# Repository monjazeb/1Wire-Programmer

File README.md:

# UNDER CONSTRUCTION
this project is not finished yet.

## Todo
- [x] GUI and Serial connection
- [ ] 1wire
    - [x] read
    - [ ] write
        - [x] change pcb to apply 12v to wire pin for write
        - [ ] edit firmware to write on chip
- [ ] EEPROM
    - [ ] read operation
        - [ ] it is erratic, why?
    - [ ] write operation
- [ ] Complete Readme.md file for help
- [ ] Create Installation package
- [ ] :tada:

## 2 in 1 Programmer1
> This project is actually a combination of 2 projects. I needed a _1Wire programmer_ and also an _EEPROM parallel programmer_. Since I had to use an _Arduino Mega_ board, I had plenty of space and `GPIO` to integrate both in one place :wink:.

You can contact me at [github](https://github.com/monjazeb) or by this [email](mailto:armonj@gmail.com).

***Thanks.***

## 1Wire Programmer
1Wire EEPROM programmer using Arduino. 

## EEPROM Progarmmer
I used [mint64](https://mint64.home.blog/2018/07/29/parallel-nor-flash-eeprom-programmer-using-an-arduino-part-1-the-sst39sf040-and-planning/)'s project as base and added essencial functionalities I needed.

## GUI

## Board

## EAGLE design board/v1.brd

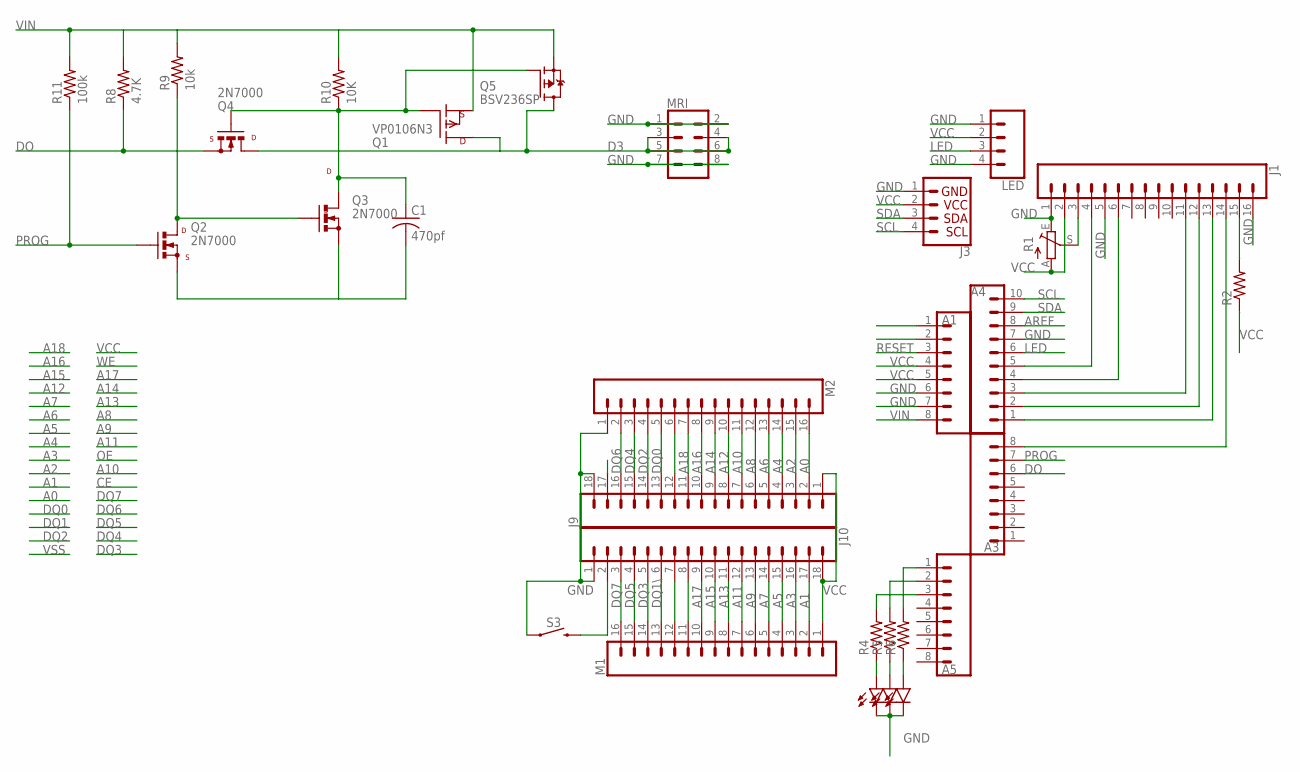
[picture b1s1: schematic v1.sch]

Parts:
A1, A3, A5: CONN_08FEMALE_LOCK; 1X08_FEMALE_LOCK
A4: CONN_10LOCK; 1X10_LOCK
C1: 470pf; C025-025X050
D1, D2, D3: LED3MM; LED_3MM
J1: CONN_16LOCK; 1X16_LOCK
J3: I2C_STANDARD; 1X04
J9, J10: CONN_18SILK; 1X18
LED: CONN_04LOCK; 1X04_LOCK
M1, M2: CONN_16MACHIINE-PIN_LOCK; 1X16_MACHINE-PIN-HEADER_LOCK.004
MRI: CONN_04X2; 2X4
Q1: VP0106N3; TO92-
Q2, Q3, Q4: 2N7000; TO92-LINE
Q5: BSV236SP; SOT363_INFINEON
R1: TRIM_EU-B64Y; B64Y
R2, R4, R5, R6: R-US_0309/10; 0309/10
R8: 4.7K; 0207/2V
R9: 10k; 0309/10
R10: 10K; 0207/2V
R11: 100k; 0309/10
S3: MOMENTARY-SWITCH-SPST-PTH-6.0MM; TACTILE_SWITCH_PTH_6.0MM

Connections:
A0: J9.2, M2.16
A1: J10.17, M1.2
A2: J9.3, M2.15
A3: J10.16, M1.3
A4: J9.4, M2.14
A5: J10.15, M1.4
A6: J9.5, M2.13
A7: J10.14, M1.5
A8: J9.6, M2.12
A9: J10.13, M1.6
A10: J9.7, M2.11
A11: J10.12, M1.7
A12: J9.8, M2.10
A13: J10.11, M1.8
A14: J9.9, M2.9
A15: J10.10, M1.9
A16: J9.10, M2.8
A17: J10.9, M1.10
A18: J9.11, M2.7
AREF: A4.8
D3: MRI.3, MRI.4, MRI.5, MRI.6, Q1.1 (D), Q4.1 (D), Q5.1 (D), Q5.2 (D), Q5.5 (D), Q5.6 (D)
DO: A3.6, Q4.3 (S), R8.1
DQ0: J9.13, M2.5
DQ1\: J10.6, M1.13
DQ2: J9.14, M2.4
DQ3: J10.5, M1.14
DQ4: J9.15, M2.3
DQ5: J10.4, M1.15
DQ6: J9.16, M2.2
DQ7: J10.3, M1.16
GND: A1.6, A1.7, A4.7, D1.K (C), D2.K (C), D3.K (C), J1.1, J1.5, J1.16, J3.1, J9.18, J10.1, LED.1, LED.4, M2.1, MRI.1, MRI.2, MRI.7, MRI.8, R1.E, S3.1
LED: A4.6, LED.3
unnamed: A4.3, J1.11
unnamed: J1.3, R1.S
unnamed: J1.15, R2.2
unnamed: A4.2, J1.12
unnamed: A4.1, J1.13
unnamed: A3.8, J1.14
unnamed: A5.1, R6.2
unnamed: A4.4, J1.6
unnamed: A4.5, J1.4
unnamed: A5.2, R5.2
unnamed: A5.3, R4.2
unnamed: D3.A, R6.1
unnamed: D2.A, R5.1
unnamed: D1.A, R4.1
unnamed: Q2.1 (D), Q3.2 (G), R9.1
unnamed: C1.2, Q2.3 (S), Q3.3 (S)
unnamed: C1.1, Q1.2 (G), Q3.1 (D), Q4.2 (G), Q5.3 (G), R10.1
unnamed: J9.12, M2.6
unnamed: J10.8, M1.11
unnamed: J10.7, M1.12
unnamed: J10.2, S3.3 (2)
PROG: A3.7, Q2.2 (G), R11.1
RESET: A1.3
SCL: A4.10, J3.4
SDA: A4.9, J3.3
VCC: A1.4, A1.5, J1.2, J3.2, J9.1, J10.18, LED.2, M1.1, R1.A, R2.1
VIN: A1.8, Q1.3 (S), Q5.4 (S), R8.2, R9.2, R10.2, R11.2

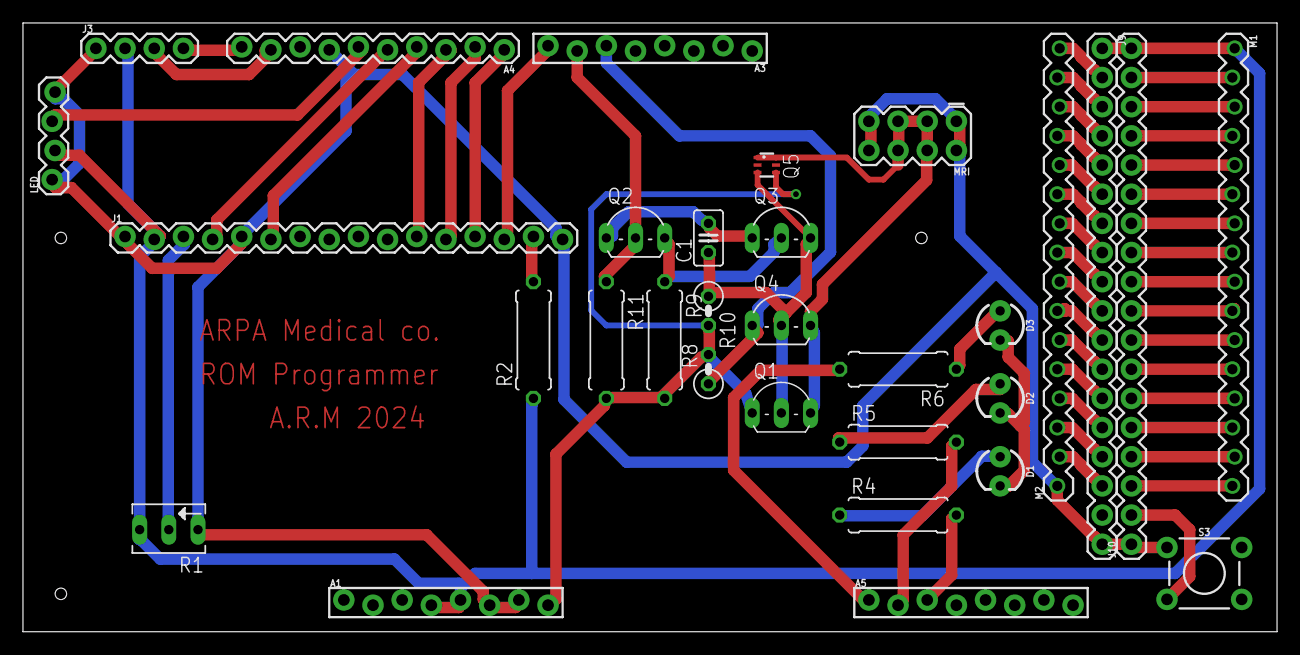
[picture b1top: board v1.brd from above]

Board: 2 copper layers, 109.2 x 53.0 mm, 31 parts (0 on the bottom side), 57 nets.

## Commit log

2024-02-20 Initial
2024-02-20 edited gitignore
2024-02-20 test development
2024-03-06 folders and organization
2024-03-06 readme.md updated
2024-03-06 add gui images
2024-03-06 readme
2024-03-12 last edits on firmware

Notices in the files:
parts and their libraries:
SparkFun-Connectors: Licensing: Creative Commons ShareAlike 4.0 International - https://creativecommons.org/licenses/by-sa/4.0
